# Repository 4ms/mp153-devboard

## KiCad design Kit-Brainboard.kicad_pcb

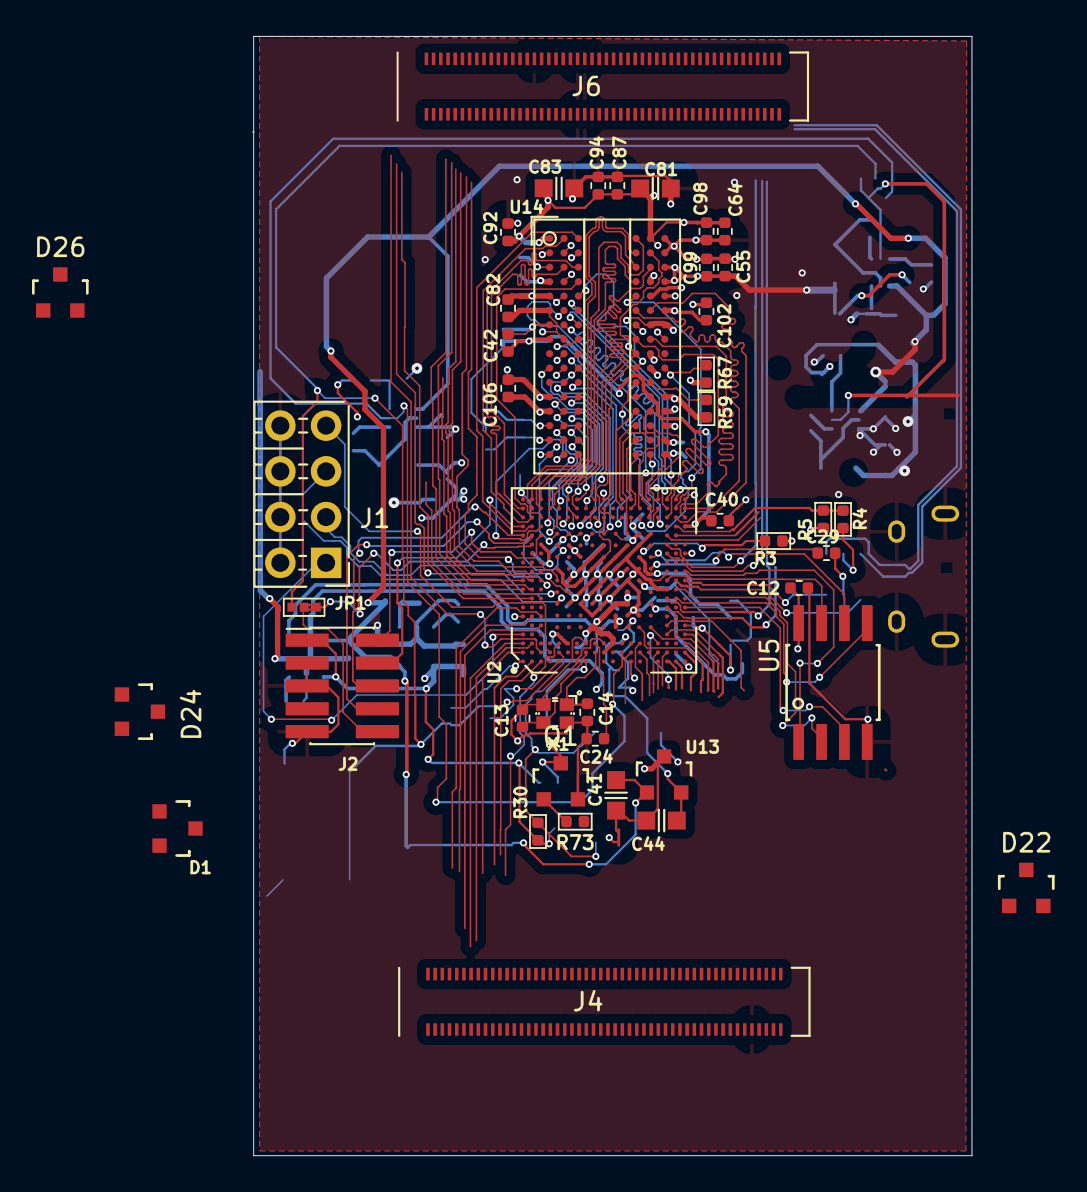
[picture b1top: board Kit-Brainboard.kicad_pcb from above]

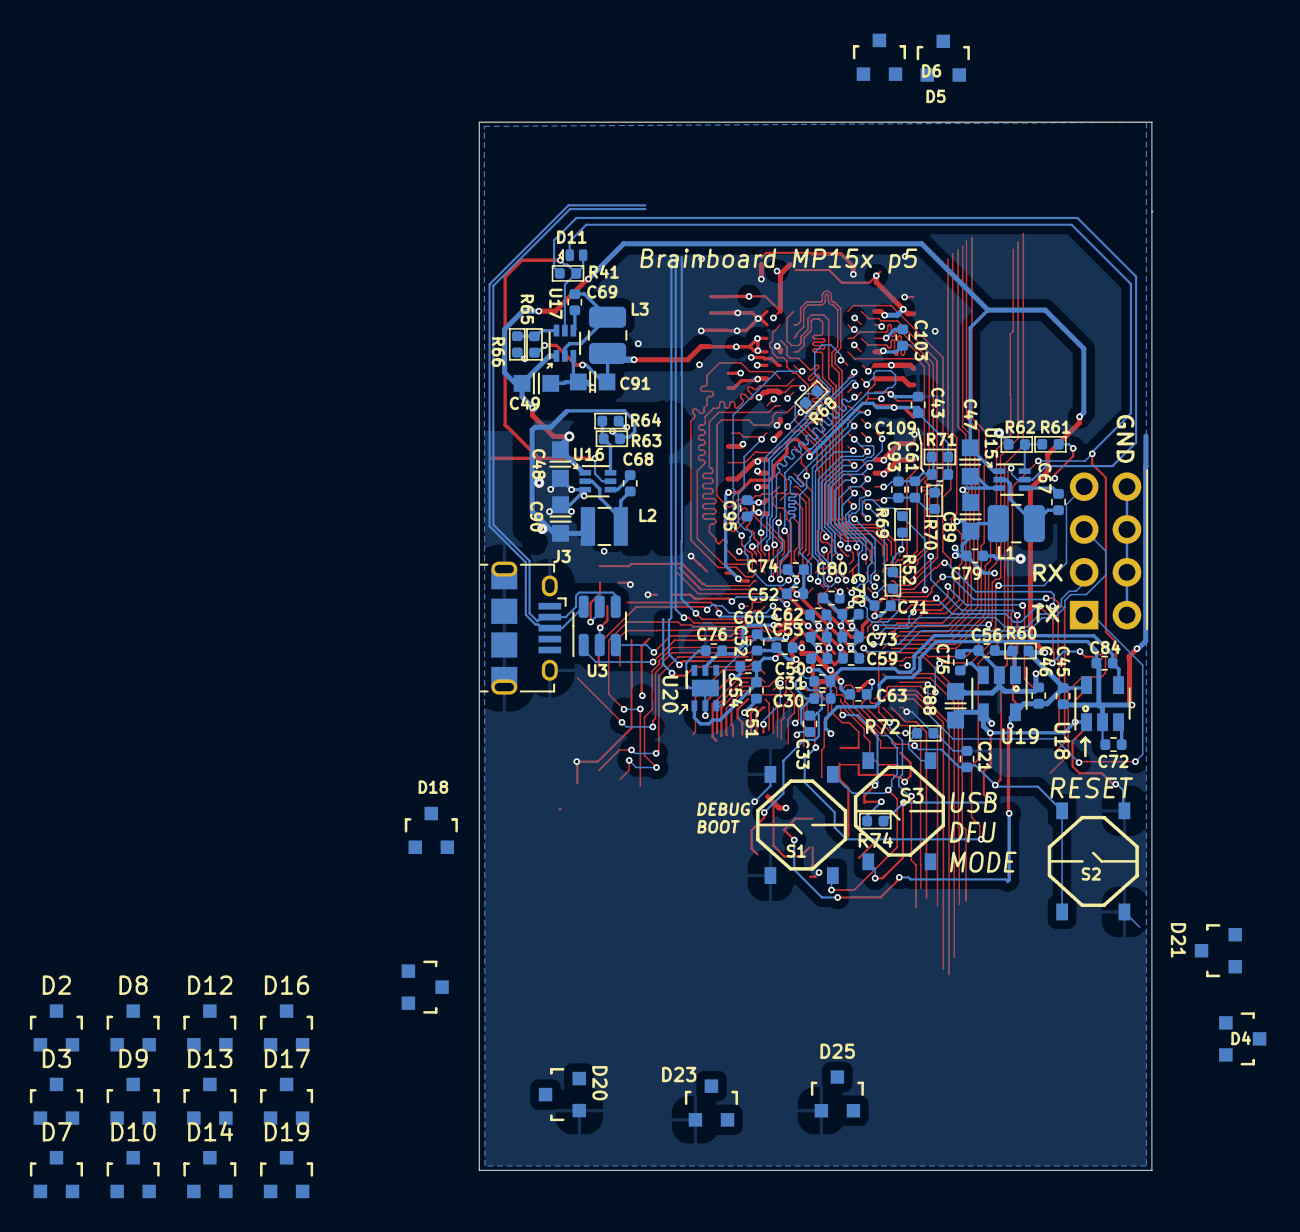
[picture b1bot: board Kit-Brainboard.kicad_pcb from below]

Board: 4 copper layers, 39.9 x 62.2 mm, 138 parts (94 on the bottom side), 150 nets.

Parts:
C12, C21, C30, C40, C42, C43, C61, C64, C67, C68, C69, C82, C87, C92, C93, C94, C95, C98, C99, C102, C103, C106: 100nF_0402_16V; C_0402
C13, C14: 6.8pF_0402_25V; C_0402
C24: 10nF_0402_16V; C_0402
C29, C32: 2.2uF_0402_6.3V; C_0402
C31, C33, C45, C46, C50, C51, C52, C53, C54, C55, C59, C60, C62, C63, C70, C73, C79, C109: 1uF_0402_25V; C_0402
C41, C47, C48, C49: 2.2uF_0603_25V; C_0603
C44, C81, C83: 10uF_0603_10V; C_0603
C56, C72, C75: 100nF_0402_50V; C_0402
C71, C74, C80: 3.3nF_0402_16V; C_0402
C76, C84: 4.7uF_0402_6.3V; C_0402
C88, C89, C90, C91: 22uF_0603_6.3V; C_0603
D1, D2, D3, D4, D5, D6, D7, D8, D9, D10, D12, D13, D14, D15, D16, D17, D18, D19, D20, D21, D22, D23, D24, D25, D26: BAT54S; SOT23-3_PO132
D11: BAT54LP; DFN-1006-2
J1: Pins_02x04_RightAngle_P2.54mm_TH; Pins_2x04_P2.54mm_Horizontal_CroppedSilk
J2: Pins_02x05_P1.27mm_SMT; Pins_2x05_1.27mm_SMD
J3: USB_B_Micro_10118194-0011LF; USB_Micro-B_Amphenol_10118194_Horizontal
J4, J6: Conn_02x50; Connector-100pin-P0.4mm-W3.0mm
JP1: SolderJumper_3_Bridged12; JUMPER_SMD_1x3_tiny
L1, L3: 1uH_3.2A_2520; L_1008_2520Metric
L2: 4.7uH_1.7A_2510; L_Wuerth_MAPI-2510
NT2: NetTie_2; NetTie-2_SMD_Pad0.16mm_6mil
Q1: MMBT3904; SOT23-3_PO132
R3: 3k_0402; R_0402
R4: 430k_0402; R_0402
R5: 620k_0402; R_0402
R30, R41, R61, R64, R66, R67, R69, R72, R74: 10k_0402; R_0402
R52, R59: 240Ω_0402; R_0402
R60, R73: 100k_0402; R_0402
R62: 20k_0402; R_0402
R63: 31.6k_0402; R_0402
R65: 6.8k_0402; R_0402
R68: 100Ω_0402; R_0402
R70, R71: 1k_0402; R_0402
S1, S2, S3: SW_Push_PTS526 SM15 SMTR2 LFS; Button_Tact_PTS526
U2: STM32MP15xxAD; TFBGA-257_10x10mm_perP0.5_cntrP0.65
U3: USBLC6-2SC6; SOT-23-6
U5: NORFLASH_W25Q128JV; SOIC-8_5.28x4.9mm_Pitch1.27mm
U13: NCP51460SN33; SOT23-3_PO132
U14: DDR3L-RAM-4Gb_MT41K256M16TW; FBGA-96_Layout2x3x16_Body8x14_P0.8mm
U15, U16, U17: AP6230xZ6; SOT-563
U18, U19: TAR5S33; SOT-23-5
U20: AP2411SN; DFN-6-1EP_2x2mm_P0.65mm_EP1x1.6mm
X1: 24MHz_8pF_2x1.6mm; Crystal_2.0x1.6mm_4pin

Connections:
+3V3: C12.1, C90.2, D1.2 (cathode), D2.2 (cathode), D3.2 (cathode), D4.2 (cathode), D5.2 (cathode), D6.2 (cathode), D7.2 (cathode), D8.2 (cathode), D9.2 (cathode), D10.2 (cathode), D12.2 (cathode), D13.2 (cathode), D14.2 (cathode), D15.2 (cathode), D16.2 (cathode), D17.2 (cathode), D18.2 (cathode), D19.2 (cathode), D20.2 (cathode), D21.2 (cathode), D22.2 (cathode), D23.2 (cathode), D24.2 (cathode), D25.2 (cathode), D26.2 (cathode), L2.2, R63.2, U5.8 (VCC)
+5V: C41.1, C45.2, C46.2, C47.2, C48.2, C49.2, J6.39, J6.40, J6.41, J6.42, R60.1, U13.1 (VI), U15.1 (VIN), U16.1 (VIN), U17.1 (VIN), U18.5 (IN), U19.5 (IN)
/ADC-IN0_DAC-OUT0: D7.3 (AK), U2.1J1 (PA4)
/ADC-IN1_DAC-OUT1: D8.3 (AK), U2.1H1 (PA5)
/ADC-IN2: D9.3 (AK), U2.T3 (PA2)
/ADC-IN3: D10.3 (AK), U2.W3 (PA6)
/ADC-IN4: D12.3 (AK), U2.N2 (PA3)
/ADC-IN5: D13.3 (AK), U2.W2 (PA7)
/ADC-IN6: D14.3 (AK), U2.U2 (PB0)
/ADC-IN7: D15.3 (AK), U2.V1 (PC5)
/ADC-IN8: D16.3 (AK), J4.25, U2.P3 (PC3)
/ADC-IN9: D17.3 (AK), U2.U4 (PC0)
/BOOT0: R30.2, R73.1, S1.3, S1.4, U2.H3 (BOOT0)
/BOOT2: Q1.3 (C), R74.2, U2.H1 (BOOT2)
/D0: D1.3 (AK), J4.1, U2.C6 (PA9)
/D1: D2.3 (AK), J4.17, U2.E3 (PE13)
/D2: D3.3 (AK), J4.7, U2.A3 (PB7)
/D3: D4.3 (AK), J4.3, U2.B6 (PB4)
/D4: D26.3 (AK), J6.13, J6.14, U2.1A5 (PD2)
/D5: D23.3 (AK), J6.60, U2.U15 (PA11)
/D6: D18.3 (AK), J6.58, U2.U5 (PB10)
/D7: D22.3 (AK), J4.27, U2.P2 (PC2)
/D8: D20.3 (AK), U2.T2 (PC1)
/D9: J6.15, J6.16, U2.1B4 (PC12)
/D10: D5.3 (AK), J6.2, U2.B8 (PA8)
/D11: D25.3 (AK), U2.U1 (PB1)
/D12: D6.3 (AK), J6.4, U2.A10 (PE4)
/D13: D19.3 (AK), J4.11, U2.A2 (PD1)
/D14: D24.3 (AK), U2.T1 (PA1)
/D15: D21.3 (AK), J4.5, U2.C5 (PD0)
/D16: J6.5, J6.6, U2.A9 (PC8)
/D17: J6.7, J6.8, U2.B9 (PC9)
/D18: J6.9, J6.10, U2.B10 (PC10)
/D19: J6.11, J6.12, U2.C11
/D20: J4.15, U2.C1 (PE12)
/D21: J6.64, U2.V15 (PA12)
/D22: J6.62, U2.C8 (PB15)
/D23: J6.56, U2.1A4 (PB14)
/DDR_A0: U2.G18 (DDR_A0), U14.N3 (A0)
/DDR_A1: U2.M19 (DDR_A1), U14.P7 (A1)
/DDR_A2: U2.F17 (DDR_A2), U14.P3 (A2)
/DDR_A3: U2.F19 (DDR_A3), U14.N2 (A3)
/DDR_A4: U2.R17 (DDR_A4), U14.P8 (A4)
/DDR_A5: U2.1C9 (DDR_A5), U14.P2 (A5)
/DDR_A6: U2.1G9 (DDR_A6), U14.R8 (A6)
/DDR_A7: U2.1A9 (DDR_A7), U14.R2 (A7)
/DDR_A8: U2.T17 (DDR_A8), U14.T8 (A8)
/DDR_A9: U2.E18 (DDR_A9), U14.R3 (A9)
/DDR_A10: U2.M17 (DDR_A10), U14.L7 (A10/AP)
/DDR_A11: U2.N19 (DDR_A11), U14.R7 (A11)
/DDR_A12: U2.M18 (DDR_A12), U14.N7 (A12/BC#)
/DDR_A13: U2.E17 (DDR_A13), U14.T3 (A13)
/DDR_A14: U2.N18 (DDR_A14), U14.T7 (A14)
/DDR_BA0: U2.G19 (DDR_BA0), U14.M2 (BA0)
/DDR_BA1: U2.P18 (DDR_BA1), U14.N8 (BA1)
/DDR_BA2: U2.H17 (DDR_BA2), U14.M3 (BA2)
/DDR_CASN: U2.J19 (DDR_CASN), U14.K3 (CAS#)
/DDR_CKE: R67.2, U2.P17 (DDR_CKE), U14.K9 (CKE)
/DDR_CLK_N: R68.2, U2.K18 (DDR_CLKN), U14.K7 (CK#)
/DDR_CLK_P: R68.1, U2.L17 (DDR_CLKP), U14.J7 (CK)
/DDR_CSN: U2.J17 (DDR_CSN), U14.L2 (CS#)
/DDR_DQ0: U2.A17 (DDR_DQ0), U14.C3 (DQU1)
/DDR_DQ1: U2.A18 (DDR_DQ1), U14.C2 (DQU3)
/DDR_DQ2: U2.C18 (DDR_DQ2), U14.A7 (DQU4)
/DDR_DQ3: U2.B16 (DDR_DQ3), U14.A3 (DQU7)
/DDR_DQ4: U2.D18 (DDR_DQ4), U14.B8 (DQU6)
/DDR_DQ5: U2.D19 (DDR_DQ5), U14.C8 (DQU2)
/DDR_DQ6: U2.C19 (DDR_DQ6), U14.D7 (DQU0)
/DDR_DQ7: U2.B17 (DDR_DQ7), U14.A2 (DQU5)
/DDR_DQ8: U2.R18 (DDR_DQ8), U14.F2 (DQL2)
/DDR_DQ9: U2.U19 (DDR_DQ9), U14.E3 (DQL0)
/DDR_DQ10: U2.T19 (DDR_DQ10), U14.G2 (DQL6)
/DDR_DQ11: U2.W18 (DDR_DQ11), U14.F7 (DQL1)
/DDR_DQ12: U2.W17 (DDR_DQ12), U14.H8 (DQL5)
/DDR_DQ13: U2.T18 (DDR_DQ13), U14.H3 (DQL4)
/DDR_DQ14: U2.U17 (DDR_DQ14), U14.H7 (DQL7)
/DDR_DQ15: U2.V17 (DDR_DQ15), U14.F8 (DQL3)
/DDR_DQM0: U2.C17 (DDR_DQM0), U14.D3 (DMU)
/DDR_DQM1: U2.V18 (DDR_DQM1), U14.E7 (DML)
/DDR_DQS0_N: U2.B18 (DDR_DQS0N), U14.B7 (DQSU#)
/DDR_DQS0_P: U2.B19 (DDR_DQS0P), U14.C7 (DQSU)
/DDR_DQS1_N: U2.U18 (DDR_DQS1N), U14.G3 (DQSL#)
/DDR_DQS1_P: U2.V19 (DDR_DQS1P), U14.F3 (DQSL)
/DDR_ODT: U2.H18 (DDR_ODT), U14.K1 (ODT)
/DDR_RASN: U2.1E9 (DDR_RASN), U14.J3 (RAS#)
/DDR_RESETN: R69.2, U2.C16 (DDR_RESETN), U14.T2 (RESET#)
/DDR_WEN: U2.J18 (DDR_WEN), U14.L3 (WE#)
/DEBUG2: J1.5, U2.1A3 (PE3)
/DEBUG3: J1.7, U2.D2 (PE11)
/DFU_BOOT: R72.1, S3.4, U2.E1 (PD8)
/FLASH_CLK: U2.1J7 (PF10), U5.6 (CLK)
/FLASH_CS: U2.W11 (PB6), U5.1 (~CS)
/FLASH_IO0: U2.V8 (PF8), U5.5 (IO0/SI)
/FLASH_IO1: U2.V9 (PF9), U5.2 (IO1/SO)
/FLASH_IO2: U2.W7 (PF7), U5.3 (IO2/~WP)
/FLASH_IO3: U2.U10 (PF6), U5.7 (IO3/~HOLD/~RESET)
/I2C2_SCL: J4.9, U2.B3 (PD7)
/I2C2_SDA: J4.13, U2.B1 (PG15)
/JTCK_SWCLK: J2.4, U2.A16 (JTCK-SWCLK)
/JTDI: J2.8, U2.B15 (JTDI)
/JTDO_SWO: J2.6, U2.A15 (JTDO-TRACESWO)
/JTMS_SWDIO: J2.2, U2.C15 (JTMS-SWDIO)
/JTRST: JP1.1 (A), U2.B14 (NJTRST)
/NRST: C21.2, D11.1 (K), JP1.3 (B), S2.3, S2.4, U2.E2 (NRST)
/NRST_CORE: C24.2, U2.J3 (NRST_CORE)
/PWR_ON: R41.1, U2.M2 (PWR_ON), U15.5 (EN)
/PWR_ONRST: D11.2 (A), R41.2, U16.5 (EN), U17.5 (EN)
/SAI_FS: J6.30, U2.U14 (PD12)
/SAI_MCLK: J6.28, U2.C2 (PE0)
/SAI_SCK: J6.26, U2.U13 (PD13)
/SAI_SD_A: J6.22, U2.U8 (PD11)
/SAI_SD_B: J6.24, U2.U7 (PG10)
/UART_RX: J1.3, U2.C10 (PC7)
/UART_TX: J1.1, U2.A4 (PC6)
/USB_HS_D+: J3.3 (D+), J6.34, U3.6 (I/O1)
/USB_HS_D-: J3.2 (D-), J6.36, U3.4 (I/O2)
/USB_HS_DM: U2.W10 (USB_DM2), U3.3 (I/O2)
/USB_HS_DP: U2.V10 (USB_DP2), U3.1 (I/O1)
/USB_RREF: R3.2, U2.1J8 (USB_RREF)
/USB_VBUS: R4.2, R5.1, U2.V16 (OTG_VBUS)
/USB_VBUS_JACK: J3.1 (VBUS), R4.1, U3.5 (VBUS)
GND: C12.2, C13.1, C14.1, C21.1, C24.1, C29.1, C32.1, C40.1, C42.2, C43.2, C46.1, C47.1, C48.1, C49.1, C50.1, C51.1, C52.1, C53.1, C54.1, C55.1, C56.2, C59.1, C60.1, C61.1, C62.1, C63.1, C64.1, C70.1, C71.2, C73.1, C74.2, C75.2, C76.1, C79.1, C80.2, C81.1, C82.1, C83.1, C87.1, C88.1, C89.1, C90.1, C91.1, C92.2, C93.1, C94.2, C95.1, C98.2, C99.2, C102.2, C103.2, C106.2, C109.1, D1.1 (Anode), D2.1 (Anode), D3.1 (Anode), D4.1 (Anode), D5.1 (Anode), D6.1 (Anode), D7.1 (Anode), D8.1 (Anode), D9.1 (Anode), D10.1 (Anode), D12.1 (Anode), D13.1 (Anode), D14.1 (Anode), D15.1 (Anode), D16.1 (Anode), D17.1 (Anode), D18.1 (Anode), D19.1 (Anode), D20.1 (Anode), D21.1 (Anode), D22.1 (Anode), D23.1 (Anode), D24.1 (Anode), D25.1 (Anode), D26.1 (Anode), J1.2, J1.4, J1.6, J1.8, J2.3, J2.5, J2.9, J3.5 (GND), J3.6 (Shield), J4.91, J6.32, J6.43, J6.44, J6.45, J6.46, NT2.2, Q1.2 (E), R3.1, R5.2, R52.2, R59.1, R62.1, R64.1, R66.1, R67.1, R69.1, R71.2, R72.2, S1.1, S1.2, S2.1, S2.2, U2.1A6 (VSS), U2.1B8 (VSS), U2.1C3 (VSS), U2.1C5 (VSS), U2.1C7 (VSS), U2.1D2 (VSS), U2.1D4 (VSS), U2.1D6 (VSS), U2.1E3 (VSS), U2.1E5 (VSS), U2.1E7 (VSS), U2.1F4 (VSS), U2.1F6 (VSS), U2.1G2 (VSS), U2.1G5 (VSS), U2.1G7 (VSS), U2.1H2 (VSS), U2.1H3 (VSS), U2.1H4 (VSS), U2.1H6 (VSS), U2.1H8 (VSS), U2.1J5 (VSS), U2.1J9 (VSS), U2.A1 (VSS), U2.A6 (VSS), U2.A19 (VSS), U2.C14 (VSS), U2.D17 (VSS), U2.F3 (VSS), U2.F18 (VSS), U2.G1 (VSS), U2.G17 (VSS), U2.K3 (BOOT1), U2.K17 (VSS), U2.K19 (VSS), U2.N1 (VSS), U2.N17 (VSS), U2.R19 (VSS), U2.U9 (VSS), U2.U11 (BYPASS_REG1V8), U2.W1 (VSS), U2.W5 (VSS), U2.W13 (VSS), U2.W19 (VSS), U3.2 (GND), U5.4 (GND), U14.A9 (VSS), U14.B1 (VSSQ), U14.B3 (VSS), U14.B9 (VSSQ), U14.D1 (VSSQ), U14.D8 (VSSQ), U14.E1 (VSS), U14.E2 (VSSQ), U14.E8 (VSSQ), U14.F9 (VSSQ), U14.G1 (VSSQ), U14.G8 (VSS), U14.G9 (VSSQ), U14.J2 (VSS), U14.J8 (VSS), U14.M1 (VSS), U14.M9 (VSS), U14.P1 (VSS), U14.P9 (VSS), U14.T1 (VSS), U14.T9 (VSS), U15.3 (GND), U16.3 (GND), U17.3 (GND), U19.2 (GND), U20.2 (GND), U20.7 (EP), X1.2, X1.4
GNDADC: C30.2, C31.1, C33.1, C41.2, C44.2, C45.1, C72.2, C84.1, NT2.1, U2.1G1 (VSSA), U13.3 (GND), U18.2 (GND)
unnamed: J2.10, JP1.2 (C)
unnamed: Q1.1 (B), R73.2
unnamed: C13.2, U2.H2 (PH0-OSC_IN), X1.3
unnamed: C14.2, U2.J2 (PH1-OSC_OUT), X1.1
unnamed: C29.2, U2.1J6 (VDDA1V1_REG)
unnamed: R52.1, U2.1A8 (DDR_ZQ)
unnamed: R59.2, U14.L8 (ZQ)
unnamed: C67.2, U15.4 (BST)
unnamed: R61.1, R62.2, U15.6 (FB)
unnamed: C67.1, L1.1, U15.2 (SW)
unnamed: C68.2, U16.4 (BST)
unnamed: R63.1, R64.2, U16.6 (FB)
unnamed: C68.1, L2.1, U16.2 (SW)
unnamed: C69.2, U17.4 (BST)
unnamed: R65.1, R66.2, U17.6 (FB)
unnamed: C69.1, L3.1, U17.2 (SW)
unnamed: C72.1, U18.3 (Noise)
unnamed: C56.1, R60.2, U19.1 (EN)
unnamed: C75.1, U19.3 (Noise)
VDD: C51.2, C54.2, C60.2, C63.2, C88.2, J2.1, R30.1, R74.1, S3.1, U2.1D1 (VBAT), U2.1E2 (VDD), U2.1F3 (VDD), U2.1G3 (VDD), U2.1G4 (VDD), U2.1J3 (VDD), U2.K2 (PDR_ON_CORE), U2.L3 (PDR_ON), U18.1 (EN), U19.4 (OUT), U20.1 (IN)
VDDA: C30.1, C31.2, C84.2, U2.1F1 (VDDA), U2.1F2 (VDDA), U18.4 (OUT)
VDDA_1V8: C32.2, U2.1H5 (VDDA1V8_REG), U20.3 (EN)
VDD_CORE: C50.2, C53.2, C59.2, C62.2, C70.2, C73.2, C79.2, C89.2, L1.2, R61.2, U2.1B3 (VDDCORE), U2.1B5 (VDDCORE), U2.1C4 (VDDCORE), U2.1C6 (VDDCORE), U2.1D3 (VDDCORE), U2.1D5 (VDDCORE), U2.1D7 (VDDCORE), U2.1E4 (VDDCORE), U2.1E6 (VDDCORE), U2.1E8 (VDDCORE), U2.1F5 (VDDCORE), U2.1F7 (VDDCORE), U2.1G6 (VDDCORE), U2.1G8 (VDDCORE)
VDD_DDR: C52.2, C55.2, C61.2, C64.2, C71.1, C74.1, C80.1, C81.2, C82.2, C83.2, C87.2, C91.2, C92.1, C93.2, C94.1, C95.2, C98.1, C99.1, C102.1, C103.1, C106.1, L3.2, R65.2, R70.1, U2.1B9 (VDDQ_DDR), U2.1D9 (VDDQ_DDR), U2.1F9 (VDDQ_DDR), U2.1H9 (VDDQ_DDR), U14.A1 (VDDQ), U14.A8 (VDDQ), U14.B2 (VDD), U14.C1 (VDDQ), U14.C9 (VDDQ), U14.D2 (VDDQ), U14.D9 (VDD), U14.E9 (VDDQ), U14.F1 (VDDQ), U14.G7 (VDD), U14.H2 (VDDQ), U14.H9 (VDDQ), U14.K2 (VDD), U14.K8 (VDD), U14.N1 (VDD), U14.N9 (VDD), U14.R1 (VDD), U14.R9 (VDD)
VDD_USB: C76.2, U2.1H7 (VDD3V3_USB), U20.5 (OUT)
VREF+: C33.2, C44.1, U2.M3 (VREF+), U13.2 (VO)
VREF_DDR: C40.2, C42.1, C43.1, C109.2, R70.2, R71.1, U2.W16 (DDR_VREF), U14.H1 (VREFDQ), U14.M8 (VREFCA)

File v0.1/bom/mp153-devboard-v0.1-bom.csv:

"Reference","Qty","Manufacturer","Part Number","Value","Footprint","Specifications","DNP"
"X1","1","ECS","ECS-240-8-37-CKM-TR3","24MHz_8pF_2x1.6mm","4ms_Crystal:Crystal_2.0x1.6mm_4pin","24MHz 8pF Crystal Resonator, 10ppm, 2016 2x1.6mm",""
"U20","1","Diodes Incorporated","AP2411SN-7","AP2411SN","4ms_Package_QFP:DFN-6-1EP_2x2mm_P0.65mm_EP1x1.6mm","",""
"U18,U19","2","Toshiba","TAR5S33TE85LF","TAR5S33","4ms_Package_SOT:SOT-23-5","LDO 3.3V, Vin >= 12V, Enable, Min Iout >= 50mA",""
"U15,U16,U17","3","Diodes Inc","AP62301Z6","AP6230xZ6","4ms_Package_SOT:SOT-563","3A, 750kHz Buck DC/DC Converter, VinMax>=12V",""
"U14","1","Micron","MT41K256M16TW-107-P-V00H","DDR3L-RAM-4Gb_MT41K256M16TW","4ms_Package_QFP:FBGA-96_Layout2x3x16_Body8x14_P0.8mm","4Gbit DDR3L",""
"U13","1","ON Semiconductor","NCP51460SN33T1G","NCP51460SN33","4ms_Package_SOT:SOT23-3_PO132","Precision 3.3V Ref 1% 18PPM 28Vmax 20mAmax",""
"U5","1","Winbond","W25Q128JVSIQ","NORFLASH_W25Q128JV","4ms_Package_SOIC:SOIC-8_5.28x4.9mm_Pitch1.27mm","16Mbit QSPI NOR FLASH, 4kb uniform sectors",""
"U3","1","STMicroelectronics","USBLC6-2SC6","USBLC6-2SC6","Package_TO_SOT_SMD:SOT-23-6","ESD Protection, pins 3+4, 1+6 shorted",""
"U2","1","STMicroelectronics","STM32MP153DAD","STM32MP15xxAD","4ms_Package_QFP:TFBGA-257_10x10mm_perP0.5_cntrP0.65","Cortex A7x2 + M4, 800MHz, TFBGA12x12",""
"S2,S3","2","C&K Switches","PTS526 SM15 SMTR2 LFS","SW_Push_PTS526 SM15 SMTR2 LFS","4ms_Switch:Button_Tact_PTS526","Tact button, NO, ",""
"R70,R71","2","Yageo","RC0402FR-071KL","1k_0402","4ms_Resistor:R_0402","1k, 1%, 1/16W, 0402",""
"R68","1","Yageo","RC0402FR-07100RL","100Ω_0402","4ms_Resistor:R_0402","100Ω, 1%, 1/16W, 0402",""
"R65","1","Yageo","RC0402FR-076K8L","6.8k_0402","4ms_Resistor:R_0402","6.8k, 1%, 1/16W, 0402",""
"R63","1","Yageo","RC0402FR-0731K6L","31.6k_0402","4ms_Resistor:R_0402","31.6k, 1%, 1/16W, 0402",""
"R62","1","Yageo","RC0402FR-0720KL","20k_0402","4ms_Resistor:R_0402","20k, 1%, 1/16W, 0402",""
"R60","1","Yageo","RC0402FR-07100KL","100k_0402","4ms_Resistor:R_0402","100k, 1%, 1/16W, 0402",""
"R52,R59","2","Yageo","RC0402FR-07240RL","240Ω_0402","4ms_Resistor:R_0402","240Ω, 1%, 1/16W, 0402",""
"R41,R61,R64,R66,R67,R69,R72","7","Yageo","RC0402FR-0710KL","10k_0402","4ms_Resistor:R_0402","10k, 1%, 1/16W, 0402",""
"R10,R11","2","Yageo","RC0402FR-075K1L","5.1k_0402","4ms_Resistor:R_0402","5.1k, 1%, 1/16W, 0402",""
"R5","1","Yageo","RC0402FR-07620KL","620k_0402","4ms_Resistor:R_0402","620k, 1%, 1/16W, 0402",""
"R4","1","Yageo","RC0402FR-07430KL","430k_0402","4ms_Resistor:R_0402","430k, 1%, 1/16W, 0402",""
"R3","1","Yageo","RC0402FR-073KL","3k_0402","4ms_Resistor:R_0402","3k, 1%, 1/16W, 0402",""
"L2","1","Bourns","SRN2510F-4R7M","4.7uH_1.7A_2510","Inductor_SMD:L_Wuerth_MAPI-2510","Power Inductors - SMD 4.7uH 20% SMD 2510 1.7A",""
"L1,L3","2","Murata","DFE252012P-1R0M=P2","1uH_3.2A_2520","Inductor_SMD:L_1008_2520Metric","Inductor 1uH ~42mohm 3.2A 2.5mm x 2.0mm",""
"J5","1","TAD","1-0201FBV0T","Conn_01x02","4ms_Connector:Pins_1x02_2.54mm_TH","Pins_01x02, Header, Male Pins, 1*2, spacing 2.54mm, straight pin",""
"J4,J6","2","Hirose","DF40C-80DP-0.4V(51)","Pins_02x40_P0.4mm_W3.0mm_SMT","mp153-devboard:Connector-80pin-P0.4mm-W3.0mm","",""
"J3","1","Molex","217179-0001","USB-C_Receptacle_Molex_2171790001","4ms_Connector:USB_C_Receptacle_Molex_2171790001","",""
"J2","1","Samtec","FTSH-105-01-F-DV","Pins_02x05_P1.27mm_SMT","4ms_Connector:Pins_2x05_1.27mm_SMD","Header 2x5 Pins, Pitch=1.27mm, Pin Height=3mm, Vertical, SMT",""
"J1","1","Samtec","TSW-104-08-T-D-RA","Pins_02x04_RightAngle_P2.54mm_TH","4ms_Connector:Pins_2x04_P2.54mm_Horizontal_CroppedSilk","HEADER 2x4 MALE PINS 0.100” 90deg Right Angle",""
"H1,H2,H3,H4","4","","","Spacer Nylon, fits 3mm hole","4ms_Hardware:MountingHole_Generic_3mm","Spacer Nylon, fits 3mm hole","DNP"
"D11","1","Diodes Inc","BAT54LP-7","BAT54LP","4ms_Diode:DFN-1006-2","Schottky, 1mm x 0.6mm, Vr >= 30V, If >= 200mA, Vf = 240mA@0.1mA",""
"CON1","1","Molex","104031-0811","microSDCon_SMT_104031-0811","4ms_Connector_Card:CardSlot_MicroSD_Molex_104031-0811","MicroSD Card Conn Horiz SMT",""
"C88,C89,C90,C91","4","Murata","GRM188R60J226MEA0J","22uF_0603_6.3V","4ms_Capacitor:C_0603","22uF, 6.3V,10%,X5R or X7R,0603",""
"C76,C84","2","Murata","GRM155R60J475ME47","4.7uF_0402_6.3V","4ms_Capacitor:C_0402","4.7uF, Min. 6.3V 20%, X7R or X5R or similar",""
"C71,C74,C80","3","Vishay","VJ0402Y332KXACW1BC","3.3nF_0402_16V","4ms_Capacitor:C_0402","3.3nF, Min. 16V 10%, X7R or X5R or similar",""
"C56,C72,C75","3","Murata","GRM155R71H104KE14D ","100nF_0402_50V","4ms_Capacitor:C_0402","0.1uF, Min. 50V 10%, X7R or X5R or similar",""
"C44,C81,C83","3","Murata","GRM188R61A106KE69D","10uF_0603_10V","4ms_Capacitor:C_0603","10uF, Min. 10V X5R 10%",""
"C41,C47,C48,C49","4","Murata","GRM188R6YA225KA12D","2.2uF_0603_25V","4ms_Capacitor:C_0603","2.2uF, Min 25V 10% X5R",""
"C31,C33,C45,C46,C50,C51,C52,C53,C54,C55,C59,C60,C62,C63,C70,C73,C79,C109","18","Taiyo Yuden","GMK105CC6105KV-F","1uF_0402_25V","4ms_Capacitor:C_0402","1uF, Min. 25V, 0402, Ceramic/MLCC",""
"C29,C32","2","Murata","GRM155R60J225KE95D","2.2uF_0402_6.3V","4ms_Capacitor:C_0402","2.2uF, Min. 6.3V 10%, X7R or X5R or similar",""
"C24","1","Yageo","CC0402KRX7R7BB103","10nF_0402_16V","4ms_Capacitor:C_0402","10nF, Min. 16V 10%, X7R or X5R or similar",""
"C13,C14","2","Yageo","CC0402CRNPO9BN6R8","6.8pF_0402_25V","4ms_Capacitor:C_0402","6.8pF, Min. 25V 10%, NP0/C0G",""
"C12,C21,C30,C40,C42,C43,C61,C64,C67,C68,C69,C82,C87,C92,C93,C94,C95,C98,C99,C102,C103,C106","22","Murata","GCM155R71C104KA55D","100nF_0402_16V","4ms_Capacitor:C_0402","0.1uF, Min. 16V 10%, X7R or X5R or similar",""
"BOOT0_2","1","CTS","219-2MST","SW_DIP_x02_CTS_219-2MST","4ms_Switch:SW_DIP_SPSTx02_CTS_219-2MSTR","DIP Switch SPST x 2, Gull wing P2.54mm, 6.7x6.55mm Body, 8.6mm Rows",""
